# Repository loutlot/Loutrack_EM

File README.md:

# Loutrack EM

**磁界ベースのドリフトレスVRトラッカー**

---

## TL;DR

IMUの積分ドリフト問題を解決するため、**磁界（EM）を使った絶対位置・姿勢トラッキング**を開発中。
VRChat等のフルボディトラッキング向け。現在M0（1軸PoC）フェーズ。

---

## 現在の進捗

| フェーズ | 内容 | 状態 |
|----------|------|------|
| **M0** | 1軸ディスクリートPoC | 🔄 電源＆受信アンプ組み立て完了、ADC接続中 |
| M1 | 3軸TDM | ⬜ |
| M1.5 | 自作コイル＆ドライバ強化 | ⬜ |
| M2 | SMD基板化（バッテリー駆動対応） | 🔄 バッテリー駆動仕様策定完了 |
| M3 | 推定アルゴリズム | ⬜ |
| M4 | 製品化 | ⬜ |

---

## なぜEMトラッキング？

### 既存技術の問題

| 方式 | 問題点 |
|------|--------|
| **IMU** | 積分ドリフトで数分〜数十分で位置がズレる |
| **光学式** | オクルージョン（遮蔽）に弱い、カメラ設置が必要 |
| **Lighthouse** | 高価、HMD依存、セットアップが複雑 |

### EMトラッキングの利点

- ✅ **ドリフトなし**: 磁界強度から直接位置を算出（積分不要）
- ✅ **遮蔽に強い**: 衣服・体を通過する
- ✅ **セットアップ簡単**: 送信アンテナ1つ置くだけ
- ✅ **低コスト化の余地**: IC数個で構成可能

### EMトラッキングの課題

- ⚠️ 金属環境での歪み（キャリブレーションで対応予定）
- ⚠️ 到達距離に限界（送信出力で調整可能）
- ⚠️ 複数トラッカー時の同期

---

## 動作原理

```
┌─────────────┐          磁界           ┌─────────────┐
│   Beacon    │  ～～～～～～～～～～→  │   Tracker   │
│  （送信）   │                         │  （受信）   │
│             │                         │             │
│ 20kHz交流   │                         │ コイルで    │
│ →コイル駆動 │                         │ 誘導電圧検出│
│ →磁界放射   │                         │ →I/Q処理   │
└─────────────┘                         │ →振幅A算出 │
                                        └─────────────┘
```

### 磁界の性質を利用

1. **磁界強度は距離の3乗に反比例** → 距離が分かる
2. **3軸送受信で方向も分かる** → 姿勢も推定可能
3. **位相も取れる** → 将来的に精度向上

### I/Q同期検波

受信信号を送信周波数と同期したsin/cosで積分し、ノイズを除去しながら振幅Aを算出。

```
A = √(I² + Q²)
```

---

## システム構成（M0）

```
┌──────────────────────────────────────────────────────────┐
│                    XIAO ESP32C3                          │
│  PWM生成（20kHz）              SPI ADC読取 → I/Q処理    │
└──────────┬───────────────────────────────┬───────────────┘
           │                               │
           ▼                               ▼
┌──────────────────┐            ┌──────────────────────────┐
│    DRV8835       │            │       MCP6022            │
│   (Hブリッジ)    │            │    (受信アンプ)          │
└────────┬─────────┘            └────────────┬─────────────┘
         │                                   │
         ▼                                   ▼
┌──────────────────┐            ┌──────────────────────────┐
│   3D11-722J      │   磁界     │       3D11-722J          │
│  (送信コイル)    │ ~~~~~~~~→  │     (受信コイル)         │
└──────────────────┘            └────────────┬─────────────┘
                                             │
                                             ▼
                                ┌──────────────────────────┐
                                │        MCP3008           │
                                │         (ADC)            │
                                └──────────────────────────┘
```

## システム構成（M2）

M2では受信機（Tracker）をバッテリー駆動化し、DEEP SLEEP機能で過放電を防止。

```
┌──────────────────────────────────────────────────────────┐
│                XIAO ESP32C3 (Tracker)                    │
│  バッテリー監視 → DEEP SLEEP      SPI ADC読取 → I/Q処理 │
└──────────┬───────────────────────────────┬───────────────┘
           │                               │
           ▼                               ▼
┌──────────────────┐            ┌──────────────────────────┐
│ Li-Po 3.7V       │            │       MCP6022            │
│ (バッテリー)     │            │    (受信アンプ)          │
└────────┬─────────┘            └────────────┬─────────────┘
         │                                   │
         ▼                                   ▼
┌──────────────────┐            ┌──────────────────────────┐
│ 電圧監視回路     │            │       3D11-722J          │
│ (200kΩ分圧)      │            │     (受信コイル)         │
└────────┬─────────┘            └────────────┬─────────────┘
         │                                   │
         ▼                                   ▼
┌──────────────────┐            ┌──────────────────────────┐
│ Wake-upボタン    │   磁界     │        MCP3008           │
│ (D1ピン)         │ ~~~~~~~~→  │         (ADC)            │
└──────────────────┘            └──────────────────────────┘
```

---

## 使用部品

| 部品 | 型番 | 役割 |
|------|------|------|
| MCU | XIAO ESP32C3 | PWM生成、ADC読取、I/Q処理 |
| 3軸コイル | 3D11-722J (7.2mH) | 送受信アンテナ |
| モータドライバ | DRV8835 | コイル駆動（Hブリッジ） |
| オペアンプ | MCP6022 | 受信信号増幅 |
| ADC | MCP3008 | 波形サンプリング |

---

## ロードマップ

### M0: 1軸PoC（現在）
- [x] 部品調達
- [x] GPIO割り当て
- [x] Vmid生成回路組み立て
- [x] 受信アンプ組み立て・動作確認
- [ ] ADC接続・動作確認
- [ ] 送信回路組み立て
- [ ] PWM生成ファームウェア
- [ ] I/Q処理ファームウェア
- [ ] 共振C最適化
- [ ] 距離・角度応答測定

### M1: 3軸TDM
- 3軸送受信でフル姿勢推定
- Time Division Multiplex（X→Y→Z切替）
- 軸間干渉対策

### M1.5: 自作コイル＆ドライバ強化
- 送信距離拡大のための自作コイル製作
- より高出力のドライバ選定・電源強化
- 3m以上のレンジを目指す

### M2: SMD基板化（バッテリー駆動対応）
- [x] バッテリー駆動仕様策定
- [x] 電圧監視回路設計
- [x] DEEP SLEEP/Wake-up実装
- [ ] 回路図設計（KiCad）
- [ ] 基板レイアウト
- [ ] 実装・動作確認

### M3: 推定アルゴリズム
- 磁界モデルに基づく位置・姿勢推定
- キャリブレーション手法

### M4: 製品化
- 無線化（BLE/ESP-NOW）
- 複数トラッカー同期
- VRChat/SteamVR連携

---

## 参考資料

### EMトラッキングの先行事例
- [Polhemus](https://polhemus.com/) - 医療・研究用EMトラッカー
- [NDI Aurora](https://www.ndigital.com/electromagnetic-tracking/) - 手術ナビゲーション

### 技術資料
- [documents/requirements/m0_poc/specification_v0.9.md](documents/requirements/m0_poc/specification_v0.9.md) - M0詳細仕様書
- [documents/requirements/m2_smd/specification.md](documents/requirements/m2_smd/specification.md) - M2バッテリー駆動仕様書
- [documents/schematics/m2_smd/tracker/power_schematic.md](documents/schematics/m2_smd/tracker/power_schematic.md) - M2電源回路図
- [documents/progress/experiment_log.md](documents/progress/m0_poc/experiment_log.md) - M0実験ログ
- [documents/datasheets/](documents/datasheets/) - 部品データシート

---

## フォルダ構成

```
Loutrack_EM/
├── README.md              # このファイル
├── documents/             # ドキュメント
│   ├── requirements/      # 仕様書（フェーズ別）
│   ├── progress/          # 進捗管理
│   ├── bom/               # 部品リスト
│   ├── schematics/        # 回路図
│   ├── assembly/          # 組み立てガイド
│   └── datasheets/        # データシート
├── firmware/              # ファームウェア
│   ├── lib/               # 共通ライブラリ
│   │   ├── battery_monitor.h/cpp    # バッテリー電圧監視
│   │   └── power_manager.h/cpp      # 電源管理（DEEP SLEEP）
│   └── m2_tracker/         # M2受信機ファームウェア
└── kicad/                 # KiCad設計ファイル
```

---

## ライセンス

TBD

---

## 連絡先

TBD

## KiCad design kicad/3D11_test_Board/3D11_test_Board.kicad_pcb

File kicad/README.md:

# KiCad 設計ファイル

このフォルダには、Loutrack EMプロジェクトで使用するKiCad設計ファイルが保存されています。

## 概要

3D11-722Jコイルをブレッドボード互換のピンヘッダーに変換するためのテストボードをKiCadで設計しています。

## フォルダ構成

```
kicad/
├── README.md                              # このファイル
├── 3D11_test_Board/                       # 単体テストボード
│   ├── 3D11_test_Board.kicad_sch          # 回路図
│   ├── 3D11_test_Board.kicad_pcb          # PCB設計
│   ├── 3D11_test_Board.kicad_pro          # プロジェクト設定
│   ├── 3D11_test_Board.kicad_prl          # プロジェクトレイアウト
│   ├── 3D11_test_Board.png                # 3Dレンダリング
│   ├── garber.zip                         # ガーバーファイル
│   └── fp-info-cache                      # フットプリントキャッシュ
└── 3D11_production/                       # 量産用パネル基板
    ├── 3d11_testboard_batch.kicad_pcb     # PCB設計（パネル）
    ├── 3d11_testboard_batch.kicad_pro     # プロジェクト設定
    ├── 3d11_testboard_batch.png           # 3Dレンダリング
    └── garber.zip                         # ガーバーファイル
```

## テストボードの目的

3D11-722JはSMD部品のため、ブレッドボード（2.54mmピッチ）で直接使用できません。このテストボードは以下の機能を果たします：

- **SMD → DIP変換**: 3D11-722Jを2.54mmピッチのピンヘッダーに接続
- **ブレッドボード互換**: 標準的なブレッドボードに挿入可能
- **信号分離**: 各軸（X, Y, Z）のコイル端子を独立してアクセス可能

## ピン配置

### 基板上面（Y軸 + X軸）

```
        ┌─────────────────────────────────────┐
        │          3D11-722J                  │
        │          Test Board                 │
        │                                     │
        │  Y- [●]  Y+ [●]  X- [●]  X+ [●]    │  ← 上部
        │                                     │
        │          [コイル実装位置]           │
        │                                     │
        │  X+ [●]  X- [●]  Z+ [●]  Z- [●]    │  ← 下部
        │                                     │
        └─────────────────────────────────────┘
```

- **上部**: Y軸, X軸（Y-, Y+, X-, X+）
- **下部**: X軸, Z軸（X+, X-, Z+, Z-）
- **注意**: X軸は上部と下部の両方に存在（接続確認用）

## バージョン説明

### 3D11_test_Board（単体版）

- **用途**: プロトタイプ開発、少量製作
- **基板サイズ**: 単体基板
- **特徴**:
  - 回路図を含む完全なKiCadプロジェクト
  - テスト用の設計検証が可能

### 3D11_production（パネル版）

- **用途**: 量産、10枚同時発注
- **基板サイズ**: 10枚パネル配置
- **特徴**:
  - パネル化によるコスト削減
  - 量産向けに最適化

## 設計仕様

### 電気的特性

| 項目 | 仕様 |
|------|------|
| 入力電圧 | コイルからの誘導電圧（AC） |
| 周波数範囲 | DC〜1MHz（3D11-722JのSRFまで） |
| インピーダンス | コイルインピーダンスに準ずる |
| 絶縁耐圧 | 基板絶縁強度による |

### 機械的特性

| 項目 | 仕様 |
|------|------|
| 基板サイズ | 約30mm × 20mm（単体） |
| 層構成 | 2層基板 |
| ピンヘッダー | 2.54mmピッチ、1×4ヘッダー × 2 |
| コイル固定 | SMDパッド + はんだ固定 |

## 製造手順

### 部品調達

| 部品 | 型番 | 数量 | 備考 |
|------|------|------|------|
| 3D11-722J | - | 1個/基板 | [AliExpress](https://ja.aliexpress.com/item/1005004723068527.html) |
| ピンヘッダー | 1×4, 2.54mm | 2個/基板 | ブレッドボード用 |

### 組み立て手順

1. **基板準備**
   - KiCadでPCBを発注
   - ガーバーファイル（garber.zip）を使用

2. **部品実装**
   - 3D11-722Jを基板中央に配置
   - SMDはんだ付けを実施
   - ピンヘッダーを上下に挿入

3. **動作確認**
   - テスターで各ピン間の導通を確認
   - ショートがないことを確認

## 使用方法

### ブレッドボードへの接続

1. ピンヘッダーをブレッドボードに挿入
2. コイルの各軸端子を回路に接続
3. 電源投入前に接続を確認

### 信号接続例（M0 PoC）

```
DRV8835出力 ──→ 3D11_test_Board X+ ──→ コイルX軸
コイルX軸 ──→ 3D11_test_Board X- ──→ MCP6022入力
```

## 設計ファイルの編集

### KiCadプロジェクトを開く

1. KiCadを起動
2. `File` → `Open Project` → `.kicad_pro`ファイルを選択
3. 回路図（.kicad_sch）またはPCB（.kicad_pcb）を編集

### 回路図の編集

- ピン配置の変更
- 追加回路の設計
- フットプリントの更新

### PCBレイアウトの編集

- 配線パターンの最適化
- サイズ変更
- 層構成の変更

## 注意事項

⚠️ **設計時の注意点:**

1. **絶縁距離**: 高周波信号のため、配線間隔を十分に確保
2. **GND接続**: ノイズ対策のため、GNDプレーンを確保
3. **熱対策**: 発熱部品がある場合は放熱パターンを考慮

⚠️ **使用時の注意点:**

1. **静電気**: ESD対策のため、取り扱いに注意
2. **電源投入**: 接続ミスがないことを確認してから電源投入
3. **周波数範囲**: 3D11-722JのSRFを超えないよう注意

## 関連ドキュメント

- [3D11-722Jデータシート](../../../../documents/datasheets/3d11_coil/)
- [M0組み立てガイド](../../../../documents/assembly/m0_poc/README.md)
- [BOM](../../../../documents/bom/m0_poc/bom.md)

## 変更履歴

| 日付 | 内容 | 変更者 |
|------|------|--------|
| 2026-01-11 | 初版作成 | - |

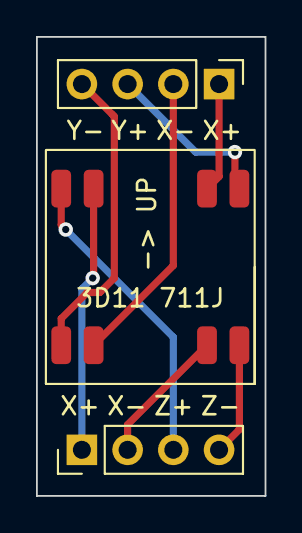
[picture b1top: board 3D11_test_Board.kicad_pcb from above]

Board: 2 copper layers, 12.7 x 25.5 mm, 3 parts (0 on the bottom side), 8 nets.

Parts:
3D11 711J: ZSUCORE_3D11-722J
JXY: Conn_01x04_MountingPin; PinHeader_1x04_P2.54mm_Vertical
JXZ: Conn_01x04_MountingPin; PinHeader_1x04_P2.54mm_Vertical

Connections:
unnamed: 3D11 711J.2 (X+), JXY.1
unnamed: 3D11 711J.6 (X-), JXY.2
unnamed: 3D11 711J.1 (Y+), JXY.3
unnamed: 3D11 711J.5 (Y-), JXY.4
unnamed: 3D11 711J.3 (X+), JXZ.1
unnamed: 3D11 711J.7 (X-), JXZ.2
unnamed: 3D11 711J.4 (Z+), JXZ.3
unnamed: 3D11 711J.8 (Z-), JXZ.4

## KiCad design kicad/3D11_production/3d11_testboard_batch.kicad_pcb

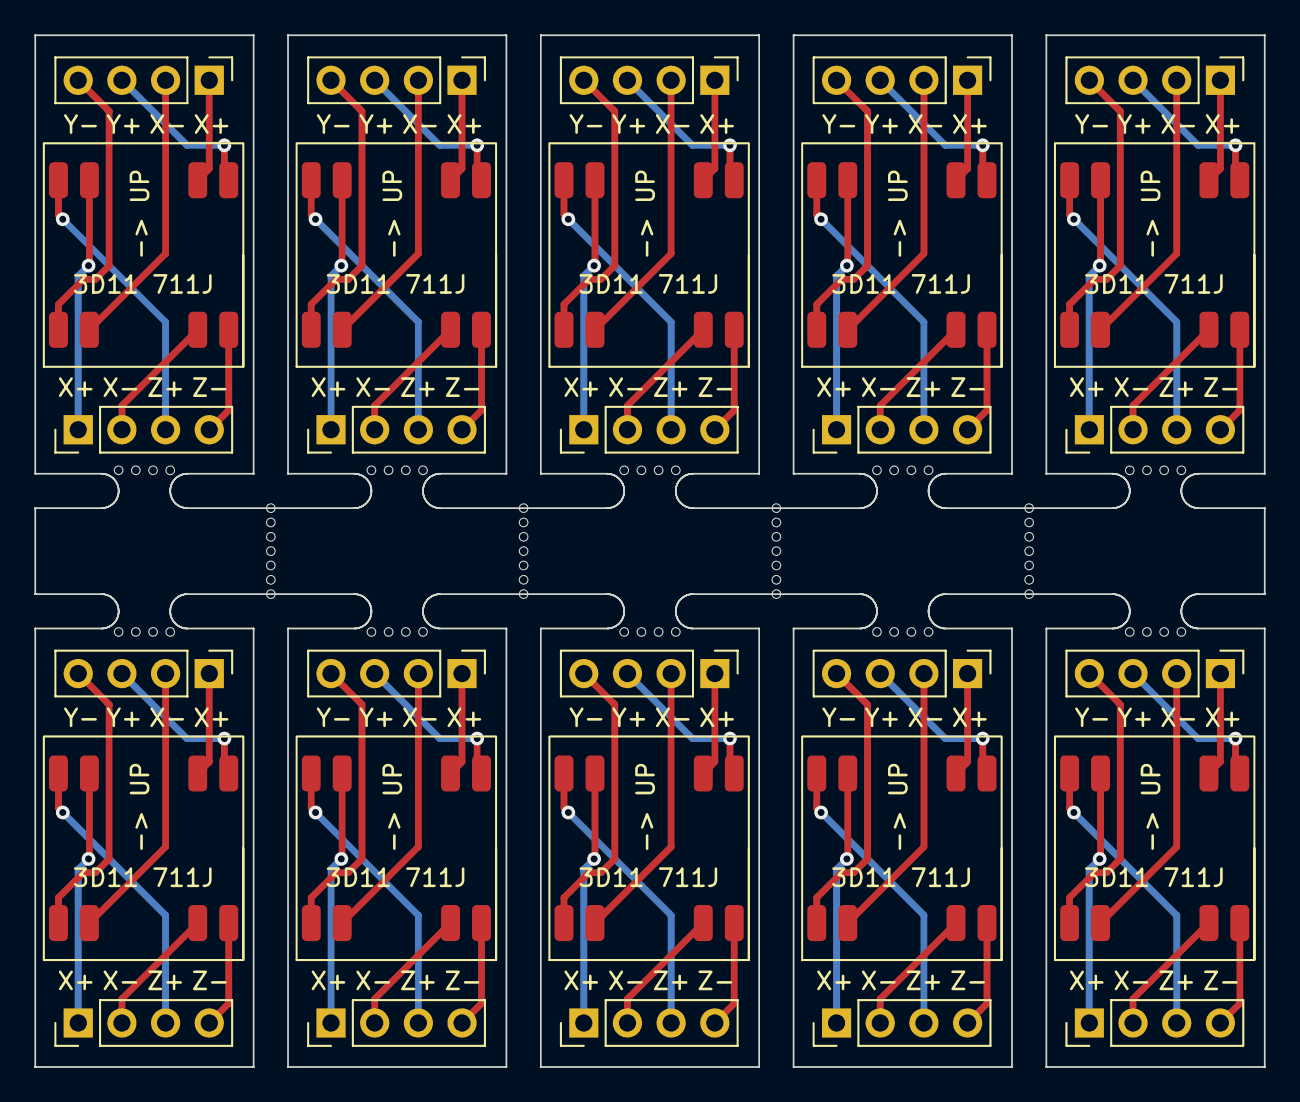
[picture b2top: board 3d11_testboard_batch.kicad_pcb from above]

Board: 2 copper layers, 71.5 x 60.0 mm, 98 parts (0 on the bottom side), 80 nets.

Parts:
3D11 711J, 3D11 711J#2, 3D11 711J#3, 3D11 711J#4, 3D11 711J#5, 3D11 711J#6, 3D11 711J#7, 3D11 711J#8, 3D11 711J#9, 3D11 711J#10: ZSUCORE_3D11-722J
JXY: Conn_01x04_MountingPin; PinHeader_1x04_P2.54mm_Vertical
JXY#2, JXY#3, JXY#4, JXY#5, JXY#6, JXY#7, JXY#8, JXY#9, JXY#10: Conn_01x04_MountingPin; PinHeader_1x04_P2.54mm_Vertical
JXZ: Conn_01x04_MountingPin; PinHeader_1x04_P2.54mm_Vertical
JXZ#2, JXZ#3, JXZ#4, JXZ#5, JXZ#6, JXZ#7, JXZ#8, JXZ#9, JXZ#10: Conn_01x04_MountingPin; PinHeader_1x04_P2.54mm_Vertical
KiKit_MB_1_1, KiKit_MB_1_2, KiKit_MB_1_3, KiKit_MB_1_4, KiKit_MB_2_1, KiKit_MB_2_2, KiKit_MB_2_3, KiKit_MB_2_4, KiKit_MB_3_1, KiKit_MB_3_2, KiKit_MB_3_3, KiKit_MB_3_4, KiKit_MB_4_1, KiKit_MB_4_2, KiKit_MB_4_3, KiKit_MB_4_4, KiKit_MB_5_1, KiKit_MB_5_2, KiKit_MB_5_3, KiKit_MB_5_4, KiKit_MB_6_1, KiKit_MB_6_2, KiKit_MB_6_3, KiKit_MB_6_4, KiKit_MB_7_1, KiKit_MB_7_2, KiKit_MB_7_3, KiKit_MB_7_4, KiKit_MB_8_1, KiKit_MB_8_2, KiKit_MB_8_3, KiKit_MB_8_4, KiKit_MB_9_1, KiKit_MB_9_2, KiKit_MB_9_3, KiKit_MB_9_4, KiKit_MB_10_1, KiKit_MB_10_2, KiKit_MB_10_3, KiKit_MB_10_4, KiKit_MB_11_1, KiKit_MB_11_2, KiKit_MB_11_3, KiKit_MB_11_4, KiKit_MB_11_5, KiKit_MB_11_6, KiKit_MB_11_7, KiKit_MB_12_1, KiKit_MB_12_2, KiKit_MB_12_3, KiKit_MB_12_4, KiKit_MB_12_5, KiKit_MB_12_6, KiKit_MB_12_7, KiKit_MB_13_1, KiKit_MB_13_2, KiKit_MB_13_3, KiKit_MB_13_4, KiKit_MB_13_5, KiKit_MB_13_6, KiKit_MB_13_7, KiKit_MB_14_1, KiKit_MB_14_2, KiKit_MB_14_3, KiKit_MB_14_4, KiKit_MB_14_5, KiKit_MB_14_6, KiKit_MB_14_7: NPTH

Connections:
Board_0-Net-(JXY-Pad1): 3D11 711J#9.2 (X+), JXY.1
Board_0-Net-(JXY-Pad2): 3D11 711J#9.6 (X-), JXY.2
Board_0-Net-(JXY-Pad3): 3D11 711J#9.1 (Y+), JXY.3
Board_0-Net-(JXY-Pad4): 3D11 711J#9.5 (Y-), JXY.4
Board_0-Net-(JXZ-Pad1): 3D11 711J#9.3 (X+), JXZ#7.1
Board_0-Net-(JXZ-Pad2): 3D11 711J#9.7 (X-), JXZ#7.2
Board_0-Net-(JXZ-Pad3): 3D11 711J#9.4 (Z+), JXZ#7.3
Board_0-Net-(JXZ-Pad4): 3D11 711J#9.8 (Z-), JXZ#7.4
Board_1-Net-(JXY-Pad1): 3D11 711J#7.2 (X+), JXY#6.1
Board_1-Net-(JXY-Pad2): 3D11 711J#7.6 (X-), JXY#6.2
Board_1-Net-(JXY-Pad3): 3D11 711J#7.1 (Y+), JXY#6.3
Board_1-Net-(JXY-Pad4): 3D11 711J#7.5 (Y-), JXY#6.4
Board_1-Net-(JXZ-Pad1): 3D11 711J#7.3 (X+), JXZ#4.1
Board_1-Net-(JXZ-Pad2): 3D11 711J#7.7 (X-), JXZ#4.2
Board_1-Net-(JXZ-Pad3): 3D11 711J#7.4 (Z+), JXZ#4.3
Board_1-Net-(JXZ-Pad4): 3D11 711J#7.8 (Z-), JXZ#4.4
Board_2-Net-(JXY-Pad1): 3D11 711J.2 (X+), JXY#3.1
Board_2-Net-(JXY-Pad2): 3D11 711J.6 (X-), JXY#3.2
Board_2-Net-(JXY-Pad3): 3D11 711J.1 (Y+), JXY#3.3
Board_2-Net-(JXY-Pad4): 3D11 711J.5 (Y-), JXY#3.4
Board_2-Net-(JXZ-Pad1): 3D11 711J.3 (X+), JXZ#9.1
Board_2-Net-(JXZ-Pad2): 3D11 711J.7 (X-), JXZ#9.2
Board_2-Net-(JXZ-Pad3): 3D11 711J.4 (Z+), JXZ#9.3
Board_2-Net-(JXZ-Pad4): 3D11 711J.8 (Z-), JXZ#9.4
Board_3-Net-(JXY-Pad1): 3D11 711J#8.2 (X+), JXY#10.1
Board_3-Net-(JXY-Pad2): 3D11 711J#8.6 (X-), JXY#10.2
Board_3-Net-(JXY-Pad3): 3D11 711J#8.1 (Y+), JXY#10.3
Board_3-Net-(JXY-Pad4): 3D11 711J#8.5 (Y-), JXY#10.4
Board_3-Net-(JXZ-Pad1): 3D11 711J#8.3 (X+), JXZ#2.1
Board_3-Net-(JXZ-Pad2): 3D11 711J#8.7 (X-), JXZ#2.2
Board_3-Net-(JXZ-Pad3): 3D11 711J#8.4 (Z+), JXZ#2.3
Board_3-Net-(JXZ-Pad4): 3D11 711J#8.8 (Z-), JXZ#2.4
Board_4-Net-(JXY-Pad1): 3D11 711J#3.2 (X+), JXY#2.1
Board_4-Net-(JXY-Pad2): 3D11 711J#3.6 (X-), JXY#2.2
Board_4-Net-(JXY-Pad3): 3D11 711J#3.1 (Y+), JXY#2.3
Board_4-Net-(JXY-Pad4): 3D11 711J#3.5 (Y-), JXY#2.4
Board_4-Net-(JXZ-Pad1): 3D11 711J#3.3 (X+), JXZ#6.1
Board_4-Net-(JXZ-Pad2): 3D11 711J#3.7 (X-), JXZ#6.2
Board_4-Net-(JXZ-Pad3): 3D11 711J#3.4 (Z+), JXZ#6.3
Board_4-Net-(JXZ-Pad4): 3D11 711J#3.8 (Z-), JXZ#6.4
Board_5-Net-(JXY-Pad1): 3D11 711J#4.2 (X+), JXY#7.1
Board_5-Net-(JXY-Pad2): 3D11 711J#4.6 (X-), JXY#7.2
Board_5-Net-(JXY-Pad3): 3D11 711J#4.1 (Y+), JXY#7.3
Board_5-Net-(JXY-Pad4): 3D11 711J#4.5 (Y-), JXY#7.4
Board_5-Net-(JXZ-Pad1): 3D11 711J#4.3 (X+), JXZ#10.1
Board_5-Net-(JXZ-Pad2): 3D11 711J#4.7 (X-), JXZ#10.2
Board_5-Net-(JXZ-Pad3): 3D11 711J#4.4 (Z+), JXZ#10.3
Board_5-Net-(JXZ-Pad4): 3D11 711J#4.8 (Z-), JXZ#10.4
Board_6-Net-(JXY-Pad1): 3D11 711J#5.2 (X+), JXY#9.1
Board_6-Net-(JXY-Pad2): 3D11 711J#5.6 (X-), JXY#9.2
Board_6-Net-(JXY-Pad3): 3D11 711J#5.1 (Y+), JXY#9.3
Board_6-Net-(JXY-Pad4): 3D11 711J#5.5 (Y-), JXY#9.4
Board_6-Net-(JXZ-Pad1): 3D11 711J#5.3 (X+), JXZ.1
Board_6-Net-(JXZ-Pad2): 3D11 711J#5.7 (X-), JXZ.2
Board_6-Net-(JXZ-Pad3): 3D11 711J#5.4 (Z+), JXZ.3
Board_6-Net-(JXZ-Pad4): 3D11 711J#5.8 (Z-), JXZ.4
Board_7-Net-(JXY-Pad1): 3D11 711J#10.2 (X+), JXY#4.1
Board_7-Net-(JXY-Pad2): 3D11 711J#10.6 (X-), JXY#4.2
Board_7-Net-(JXY-Pad3): 3D11 711J#10.1 (Y+), JXY#4.3
Board_7-Net-(JXY-Pad4): 3D11 711J#10.5 (Y-), JXY#4.4
Board_7-Net-(JXZ-Pad1): 3D11 711J#10.3 (X+), JXZ#5.1
Board_7-Net-(JXZ-Pad2): 3D11 711J#10.7 (X-), JXZ#5.2
Board_7-Net-(JXZ-Pad3): 3D11 711J#10.4 (Z+), JXZ#5.3
Board_7-Net-(JXZ-Pad4): 3D11 711J#10.8 (Z-), JXZ#5.4
Board_8-Net-(JXY-Pad1): 3D11 711J#2.2 (X+), JXY#5.1
Board_8-Net-(JXY-Pad2): 3D11 711J#2.6 (X-), JXY#5.2
Board_8-Net-(JXY-Pad3): 3D11 711J#2.1 (Y+), JXY#5.3
Board_8-Net-(JXY-Pad4): 3D11 711J#2.5 (Y-), JXY#5.4
Board_8-Net-(JXZ-Pad1): 3D11 711J#2.3 (X+), JXZ#8.1
Board_8-Net-(JXZ-Pad2): 3D11 711J#2.7 (X-), JXZ#8.2
Board_8-Net-(JXZ-Pad3): 3D11 711J#2.4 (Z+), JXZ#8.3
Board_8-Net-(JXZ-Pad4): 3D11 711J#2.8 (Z-), JXZ#8.4
Board_9-Net-(JXY-Pad1): 3D11 711J#6.2 (X+), JXY#8.1
Board_9-Net-(JXY-Pad2): 3D11 711J#6.6 (X-), JXY#8.2
Board_9-Net-(JXY-Pad3): 3D11 711J#6.1 (Y+), JXY#8.3
Board_9-Net-(JXY-Pad4): 3D11 711J#6.5 (Y-), JXY#8.4
Board_9-Net-(JXZ-Pad1): 3D11 711J#6.3 (X+), JXZ#3.1
Board_9-Net-(JXZ-Pad2): 3D11 711J#6.7 (X-), JXZ#3.2
Board_9-Net-(JXZ-Pad3): 3D11 711J#6.4 (Z+), JXZ#3.3
Board_9-Net-(JXZ-Pad4): 3D11 711J#6.8 (Z-), JXZ#3.4

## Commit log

2026-01-06 Initial commit: Loutrack EM project setup
    - Project documentation structure
    - M0 PoC specifications and assembly guides
    - BOM with XIAO ESP32C3, 3D11-722J, DRV8835, MCP6022, MCP3008
    - Datasheets (DRV8835, 3D11 coil, MCP3008)
    - Wiring tables and block diagrams
2026-01-06 Add M1.5 phase: Custom coil & driver enhancement
    - Add m1.5_coil_power folders across all document categories
    - Create M1.5 specification (coil design, driver selection, power supply)
    - Update milestone tracking with M1.5 tasks
    - Update project rules and READMEs with new phase
    - Target: 3m+ range with custom coil and high-power driver
2026-01-06 Update inventory: XIAO ESP32C3 x2, 3D11-722J x5
    - Update BOM with actual inventory counts
    - XIAO ESP32C3: 2 units (M0 uses 1, 1 spare for M1+)
    - 3D11-722J: 5 units (M0 uses 2, M1 uses 2, 1 spare)
    - M1 BOM updated: no additional coil purchase needed
2026-01-06 Update M1 BOM: add inventory remaining column
2026-01-06 Add links to Akizuki product codes in BOM tables
    - Add clickable links to all Akizuki product codes
    - Format: [code](https://akizukidenshi.com/catalog/g/g[code]/)
    - Updated m0_poc/bom.md and m1_3axis/bom.md
2026-01-10 docs: 3D11-722Jテストボードの情報を追加
    - KiCad設計ファイル（単体版・パネル版）を追加
    - README.mdにテストボードの説明と組み立て手順を追加
    - 04_tx_driver.mdと05_integration.mdにテストボード使用を明記
    - BOMにテストボード情報を追加
2026-01-10 fix: 3D11-722JテストボードのKiCadファイルパスを修正
    - documents/assembly/m0_poc/から見た相対パスを../../kicad/から../../../kicad/に修正
    - README.md, 04_tx_driver.md, 05_integration.md, bom.mdを更新
2026-01-10 M2: バッテリー駆動仕様策定とファームウェア実装
    - M2仕様書にGPIO割り当てとバッテリー駆動仕様を追加
    - 電源回路図を作成（電圧監視、Wake-up回路）
    - バッテリー電圧監視ライブラリ実装
    - DEEP SLEEP/Wake-up機能実装
    - M0: 受信アンプ動作確認完了（実験ログ更新）
2026-01-10 README.md: M0/M2進捗更新とバッテリー駆動構成図追加
    - M0進捗: 電源＆受信アンプ完了、ADC接続中に更新
    - M2進捗: バッテリー駆動仕様策定完了に更新
    - M2システム構成図（バッテリー駆動対応）を追加
    - ロードマップの詳細化（M0タスク個別記載、M2バッテリー機能追加）
    - 技術資料にM2仕様書・電源回路図・実験ログを追加
    - フォルダ構成にfirmware/詳細構造を追加
2026-01-10 XIAO ESP32C3ピンアウト情報修正とデータシートREADME更新
    - wiring_table.md: XIAO ESP32C3ピン配置図の修正
    - D3-D6のGPIO/ピン割り当てを正しいものに更新
    - 左側/右側のピン配置説明を追加
    - 01_power_vmid.md: ピン配置図にSPI機能説明を追加
    - datasheets/README.md: ダウンロード済みファイル情報を更新
    - ESP32C3ピン図、MCP6022データシート、3D11コイルデータを反映
2026-01-10 KiCadフォルダにREADME.mdを追加
    - 3D11_test_Boardと3D11_productionプロジェクトの説明
    - テストボードの目的とピン配置図
    - 設計仕様、製造手順、使用方法
    - KiCadプロジェクトの編集方法
    - 関連ドキュメントへのリンク
2026-01-12 .gitignore: documents/outside_sources/を追加
    - 外部ソースフォルダをGit管理から除外
    - 著作権/ライセンス関連の懸念があるファイルを管理対象外に
2026-01-12 Add reformatted Kirb lecture document
    - Create structured Markdown version of electromagnetic 6-DOF tracking lecture
    - Organize content into logical sections with table of contents
    - Extract technical specifications and component details
    - Add references and related systems information
    - Improve readability while preserving original content
2026-01-12 Add LIS3DH integration for hemispheric ambiguity resolution
    - Update M1 milestone tracking with LIS3DH tasks (1.7-1.9)
    - Add LIS3DH to M1 BOM and create M2 SMD BOM
    - Create LIS3DH integration specification for M1
    - Update M0 spec with hemispheric ambiguity solution
    - Add M2 SMD LIS3DH schematic and BOM
    - Update README files across documentation structure
